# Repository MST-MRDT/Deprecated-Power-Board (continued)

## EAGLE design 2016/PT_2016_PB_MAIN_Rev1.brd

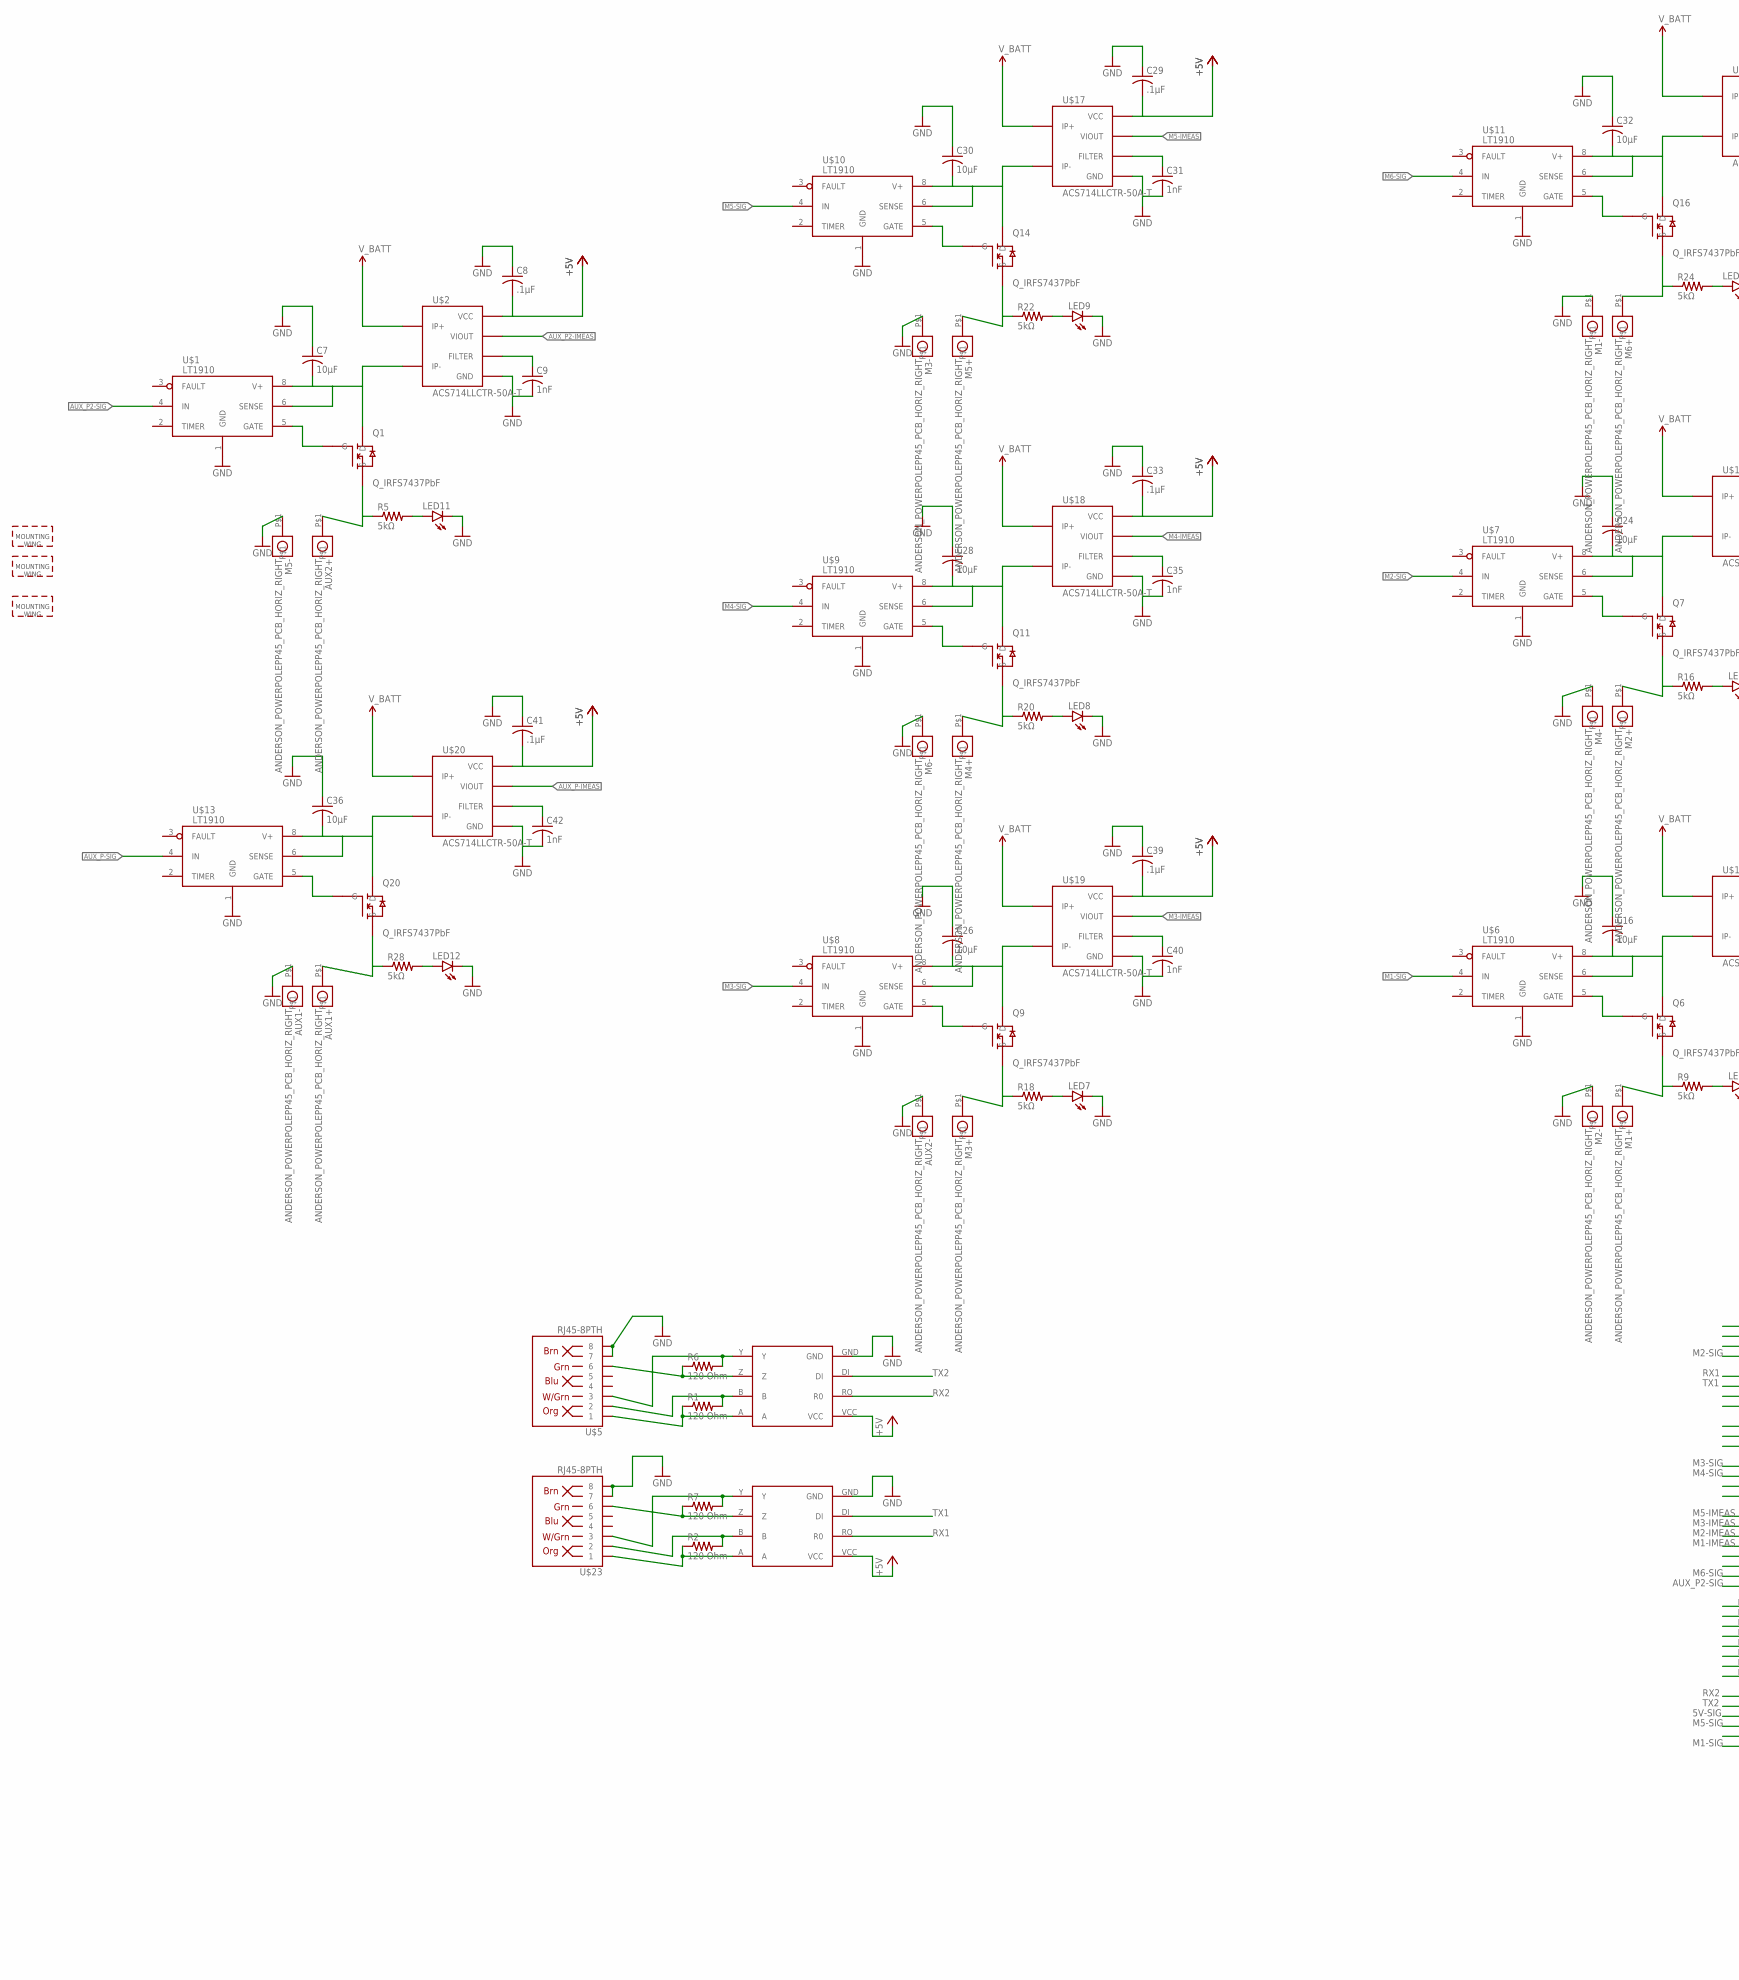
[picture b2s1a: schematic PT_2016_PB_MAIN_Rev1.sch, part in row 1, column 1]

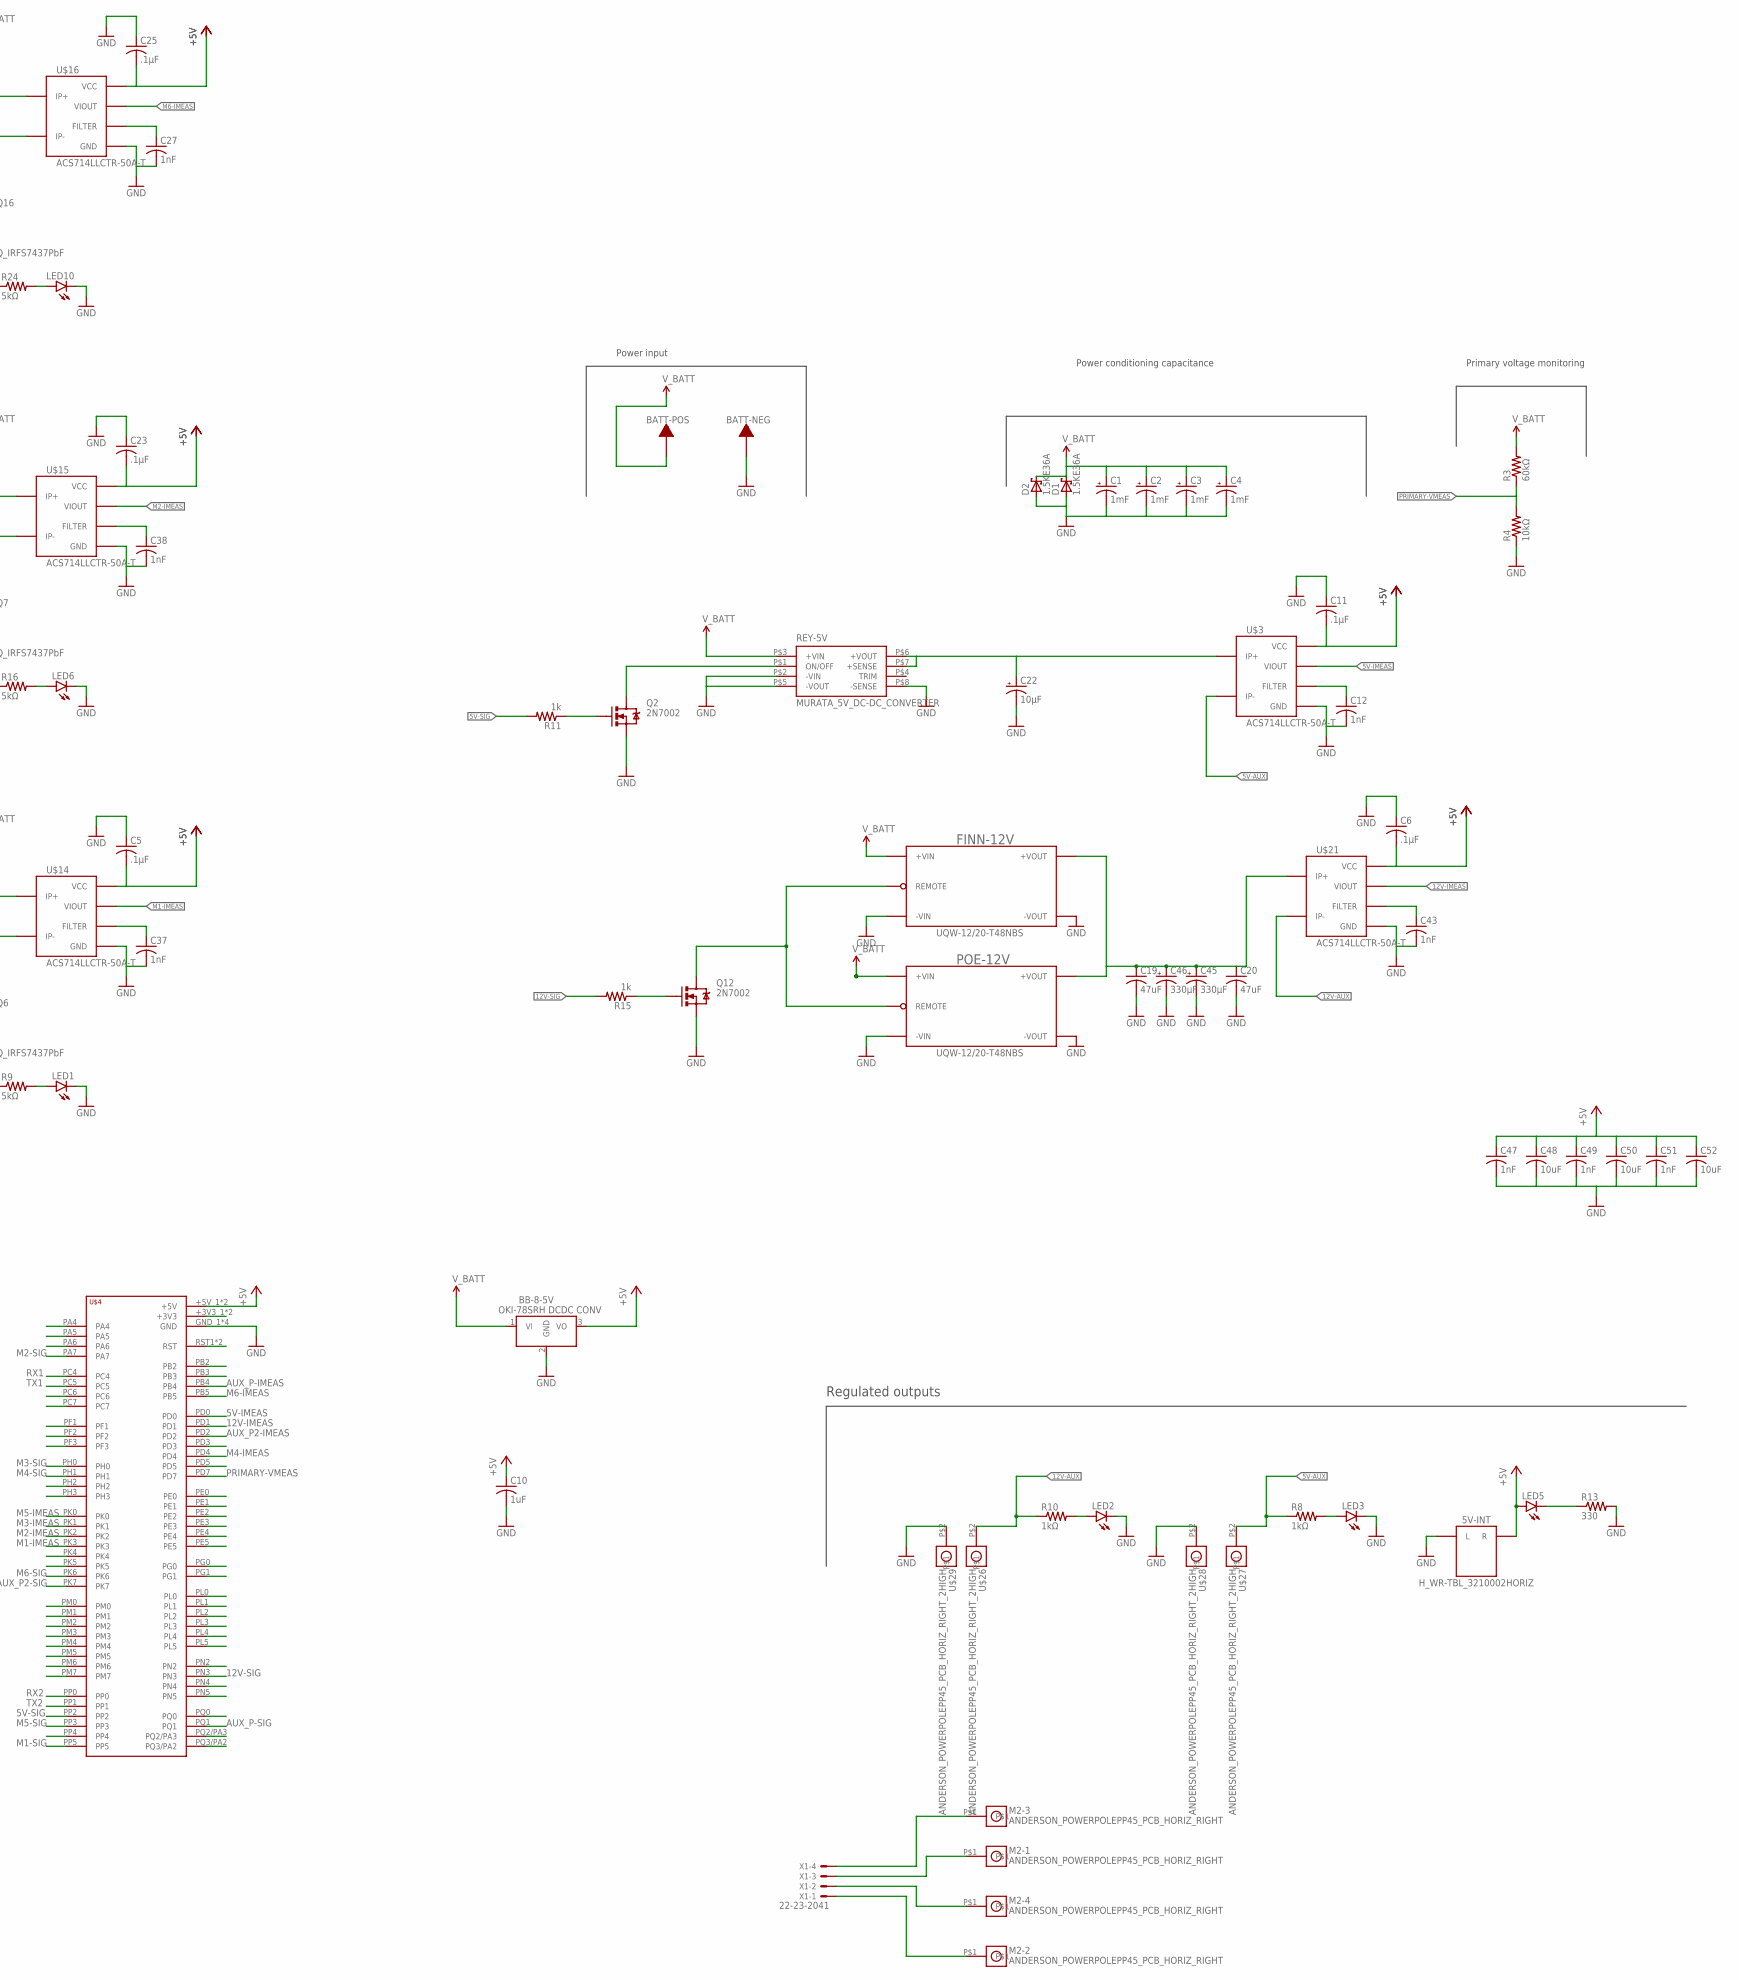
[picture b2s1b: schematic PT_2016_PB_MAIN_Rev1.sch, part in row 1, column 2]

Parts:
5V-INT: H_WR-TBL_3210002HORIZ; 691322110002
AUX1+, AUX1-, AUX2+, AUX2-: ANDERSON_POWERPOLEPP45_PCB_HORIZ_RIGHT; APP45_PCB_HORIZ_RIGHT
BATT-NEG: TERMINAL_HOLE; LARGE_TERMINAL_HOLE
BATT-POS: TERMINAL_HOLE; LARGE_TERMINAL_HOLE
BB-8-5V: Q_OKI-78SR; OKI-78SRH
C1, C2, C3, C4: 1mF; C_12.5MM
C5, C6, C8, C11, C23, C25, C29, C33, C39, C41: .1µF; C1206
C7, C16, C24, C26, C28, C30, C32, C36: 10µF; C1206
C9, C12, C27, C31, C35, C37, C38, C40, C42, C43, C47, C49, C51: 1nF; C1206
C10: 1uF; C1206
C19, C20: 47uF; C1206
C22: 10µF; E5-8,5
C45, C46: 330µF; E5-8,5
C48, C50, C52: 10uF; C1206
D1, D2: 1.5KE36A; CB429-17
FINN-12V: UQW-12/20-T48NBS; U-T48-QB-NO_TRIM
LED1, LED2, LED3, LED5, LED6, LED7, LED8, LED9, LED10, LED11, LED12: LED1206; LED-1206
M1+, M1-, M2+, M2-, M2-1, M2-2, M2-3, M2-4, M3+, M3-, M4+, M4-, M5+, M5-, M6+, M6-: ANDERSON_POWERPOLEPP45_PCB_HORIZ_RIGHT; APP45_PCB_HORIZ_RIGHT
POE-12V: UQW-12/20-T48NBS; U-T48-QB-NO_TRIM
Q1, Q6, Q7, Q9, Q11, Q14, Q16, Q20: Q_IRFS7437PbF; D2PACK
Q2, Q12: 2N7002; SOT323
R1, R2, R6, R7: 120 Ohm; 1206
R3: 60kΩ; R1206
R4: 10kΩ; R1206
R5, R9, R16, R18, R20, R22, R24, R28: 5kΩ; 1206
R8, R10: 1kΩ; 1206
R11, R15: 1k; R1206
R13: 330; 1206
REY-5V: MURATA_5V_DC-DC_CONVERTER
U$1, U$6, U$7, U$8, U$9, U$10, U$11, U$13: LT1910; SO8
U$2, U$14, U$15, U$16, U$17, U$18, U$19, U$20: ACS714LLCTR-50A-T; SOIC8_ACS711_SKETCH
U$3, U$21: ACS714LLCTR-50A-T; SOIC8_ACS711
U$4: TIVA-C-CONNECTED
U$5, U$23: RJ45-8PTH; RJ45-8
U$12, U$24: MAX3077; MAX3070E
U$25, U$41, U$42: APP_MOUTING_WINGHORIZ; APP45_MOUNTING_WING_HORIZ
U$26, U$27, U$28, U$29: ANDERSON_POWERPOLEPP45_PCB_HORIZ_RIGHT_2HIGH; APP45_PCB_HORIZ_RIGHT_2HIGH
X1: 22-23-2041

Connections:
5V-AUX: R8.1, U$3.4 (IP-), U$27.P$2
5V-IMEAS: U$3.7 (VIOUT), U$4.PD0
5V-SIG: R11.2, U$4.PP2
12V-AUX: R10.1, U$21.4 (IP-), U$26.P$2
12V-IMEAS: U$4.PD1, U$21.7 (VIOUT)
12V-SIG: R15.2, U$4.PN3
+5V: 5V-INT.R, BB-8-5V.3 (VO), C5.2, C6.2, C8.2, C10.1, C11.2, C23.2, C25.2, C29.2, C33.2, C39.2, C41.2, C47.1, C48.1, C49.1, C50.1, C51.1, C52.1, LED5.A, U$2.8 (VCC), U$3.8 (VCC), U$4.+5V_1 (+5V), U$4.+5V_2 (+5V), U$12.VCC, U$14.8 (VCC), U$15.8 (VCC), U$16.8 (VCC), U$17.8 (VCC), U$18.8 (VCC), U$19.8 (VCC), U$20.8 (VCC), U$21.8 (VCC), U$24.VCC
AUX_P2-IMEAS: U$2.7 (VIOUT), U$4.PD2
AUX_P2-SIG: U$1.4 (IN), U$4.PK7
AUX_P-IMEAS: U$4.PB4, U$20.7 (VIOUT)
AUX_P-SIG: U$4.PQ1, U$13.4 (IN)
GND: 5V-INT.L, AUX1-.P$1, AUX2-.P$1, BATT-NEG.P$1, BB-8-5V.2 (GND), C1.-, C2.-, C3.-, C4.-, C5.1, C6.1, C7.1, C8.1, C9.2, C10.2, C11.1, C12.2, C16.1, C19.2, C20.2, C22.-, C23.1, C24.1, C25.1, C26.1, C27.2, C28.1, C29.1, C30.1, C31.2, C32.1, C33.1, C35.2, C36.1, C37.2, C38.2, C39.1, C40.2, C41.1, C42.2, C43.2, C45.-, C46.-, C47.2, C48.2, C49.2, C50.2, C51.2, C52.2, D1.A, D2.A, FINN-12V.3 (-VIN), FINN-12V.4 (-VOUT), LED1.C, LED2.C, LED3.C, LED6.C, LED7.C, LED8.C, LED9.C, LED10.C, LED11.C, LED12.C, M1-.P$1, M2-.P$1, M3-.P$1, M4-.P$1, M5-.P$1, M6-.P$1, POE-12V.3 (-VIN), POE-12V.4 (-VOUT), Q2.2 (S), Q12.2 (S), R4.1, R13.2, REY-5V.P$2 (-VIN), REY-5V.P$5 (-VOUT), REY-5V.P$8 (-SENSE), U$1.1 (GND), U$2.5 (GND), U$3.5 (GND), U$4.GND_1 (GND), U$4.GND_2 (GND), U$4.GND_3 (GND), U$4.GND_4 (GND), U$5.7, U$5.8, U$6.1 (GND), U$7.1 (GND), U$8.1 (GND), U$9.1 (GND), U$10.1 (GND), U$11.1 (GND), U$12.GND, U$13.1 (GND), U$14.5 (GND), U$15.5 (GND), U$16.5 (GND), U$17.5 (GND), U$18.5 (GND), U$19.5 (GND), U$20.5 (GND), U$21.5 (GND), U$23.7, U$23.8, U$24.GND, U$28.P$2, U$29.P$2
M1-IMEAS: U$4.PK3, U$14.7 (VIOUT)
M1-SIG: U$4.PP5, U$6.4 (IN)
M2-IMEAS: U$4.PK2, U$15.7 (VIOUT)
M2-SIG: U$4.PA7, U$7.4 (IN)
M3-IMEAS: U$4.PK1, U$19.7 (VIOUT)
M3-SIG: U$4.PH0, U$8.4 (IN)
M4-IMEAS: U$4.PD4, U$18.7 (VIOUT)
M4-SIG: U$4.PH1, U$9.4 (IN)
M5-IMEAS: U$4.PK0, U$17.7 (VIOUT)
M5-SIG: U$4.PP3, U$10.4 (IN)
M6-IMEAS: U$4.PB5, U$16.7 (VIOUT)
M6-SIG: U$4.PK6, U$11.4 (IN)
unnamed: C37.1, U$14.6 (FILTER)
unnamed: C38.1, U$15.6 (FILTER)
unnamed: M2-3.P$1, X1.4
unnamed: FINN-12V.2 (REMOTE), POE-12V.2 (REMOTE), Q12.3 (D)
unnamed: M2-1.P$1, X1.3
unnamed: LED5.C, R13.1
unnamed: C22.+, REY-5V.P$6 (+VOUT), REY-5V.P$7 (+SENSE), U$3.1 (IP+)
unnamed: M2-4.P$1, X1.2
unnamed: C7.2, Q1.TAB (D), U$1.6 (SENSE), U$1.8 (V+), U$2.4 (IP-)
unnamed: AUX2+.P$1, Q1.2 (S), R5.1
unnamed: M2-2.P$1, X1.1
unnamed: C43.1, U$21.6 (FILTER)
unnamed: Q1.1 (G), U$1.5 (GATE)
unnamed: LED11.A, R5.2
unnamed: C9.1, U$2.6 (FILTER)
unnamed: C27.1, U$16.6 (FILTER)
unnamed: C31.1, U$17.6 (FILTER)
unnamed: C35.1, U$18.6 (FILTER)
unnamed: C40.1, U$19.6 (FILTER)
unnamed: C42.1, U$20.6 (FILTER)
unnamed: C24.2, Q7.TAB (D), U$7.6 (SENSE), U$7.8 (V+), U$15.4 (IP-)
unnamed: M2+.P$1, Q7.2 (S), R16.1
unnamed: Q7.1 (G), U$7.5 (GATE)
unnamed: LED6.A, R16.2
unnamed: C19.1, C20.1, C45.+, C46.+, FINN-12V.8 (+VOUT), POE-12V.8 (+VOUT), U$21.1 (IP+)
unnamed: LED3.A, R8.2
unnamed: C12.1, U$3.6 (FILTER)
unnamed: LED1.A, R9.2
unnamed: C16.2, Q6.TAB (D), U$6.6 (SENSE), U$6.8 (V+), U$14.4 (IP-)
unnamed: M1+.P$1, Q6.2 (S), R9.1
unnamed: Q6.1 (G), U$6.5 (GATE)
unnamed: Q2.3 (D), REY-5V.P$1 (ON/OFF)
unnamed: C26.2, Q9.TAB (D), U$8.6 (SENSE), U$8.8 (V+), U$19.4 (IP-)
unnamed: M3+.P$1, Q9.2 (S), R18.1
unnamed: LED2.A, R10.2
unnamed: Q9.1 (G), U$8.5 (GATE)
unnamed: Q2.1 (G), R11.1
unnamed: LED7.A, R18.2
unnamed: C28.2, Q11.TAB (D), U$9.6 (SENSE), U$9.8 (V+), U$18.4 (IP-)
unnamed: M4+.P$1, Q11.2 (S), R20.1
unnamed: Q11.1 (G), U$9.5 (GATE)
unnamed: LED8.A, R20.2
unnamed: C30.2, Q14.TAB (D), U$10.6 (SENSE), U$10.8 (V+), U$17.4 (IP-)
unnamed: M5+.P$1, Q14.2 (S), R22.1
unnamed: Q14.1 (G), U$10.5 (GATE)
unnamed: LED9.A, R22.2
unnamed: C32.2, Q16.TAB (D), U$11.6 (SENSE), U$11.8 (V+), U$16.4 (IP-)
unnamed: M6+.P$1, Q16.2 (S), R24.1
unnamed: Q16.1 (G), U$11.5 (GATE)
unnamed: LED10.A, R24.2
unnamed: C36.2, Q20.TAB (D), U$13.6 (SENSE), U$13.8 (V+), U$20.4 (IP-)
unnamed: AUX1+.P$1, Q20.2 (S), R28.1
unnamed: Q20.1 (G), U$13.5 (GATE)
unnamed: LED12.A, R28.2
unnamed: U$4.+3V3_1 (+3V3), U$4.+3V3_2 (+3V3)
unnamed: U$4.RST1 (RST), U$4.RST_2 (RST)
unnamed: Q12.1 (G), R15.1
PRIMARY-VMEAS: R3.1, R4.2, U$4.PD7
REC+: R1.1, U$5.1, U$12.A
REC+1: R2.1, U$23.1, U$24.A
REC-: R1.2, U$5.2, U$12.B
REC-1: R2.2, U$23.2, U$24.B
RX1: U$4.PC4, U$24.RO (R0)
RX2: U$4.PP0, U$12.RO (R0)
TRANS+: R6.2, U$5.3, U$12.Y
TRANS+1: R7.2, U$23.3, U$24.Y
TRANS-: R6.1, U$5.6, U$12.Z
TRANS-1: R7.1, U$23.6, U$24.Z
TX1: U$4.PC5, U$24.DI
TX2: U$4.PP1, U$12.DI
V_BATT: BATT-POS.P$1, BB-8-5V.1 (VI), C1.+, C2.+, C3.+, C4.+, D1.C, D2.C, FINN-12V.1 (+VIN), POE-12V.1 (+VIN), R3.2, REY-5V.P$3 (+VIN), U$2.1 (IP+), U$14.1 (IP+), U$15.1 (IP+), U$16.1 (IP+), U$17.1 (IP+), U$18.1 (IP+), U$19.1 (IP+), U$20.1 (IP+)

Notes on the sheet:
Primary voltage monitoring
Power conditioning capacitance
Power input
Regulated outputs

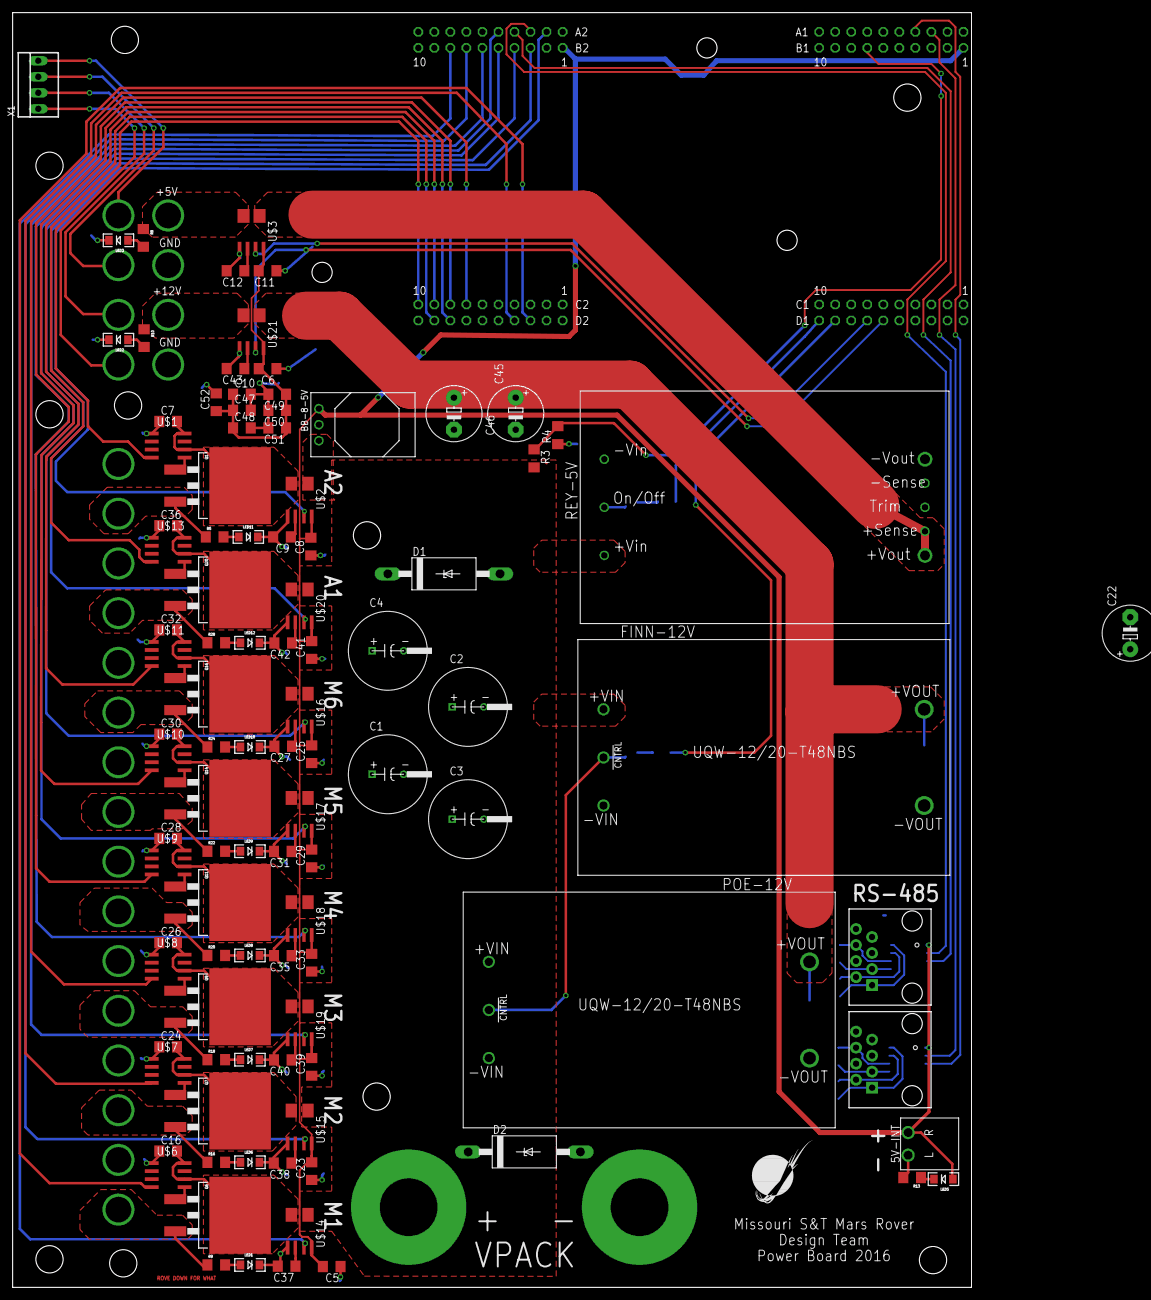
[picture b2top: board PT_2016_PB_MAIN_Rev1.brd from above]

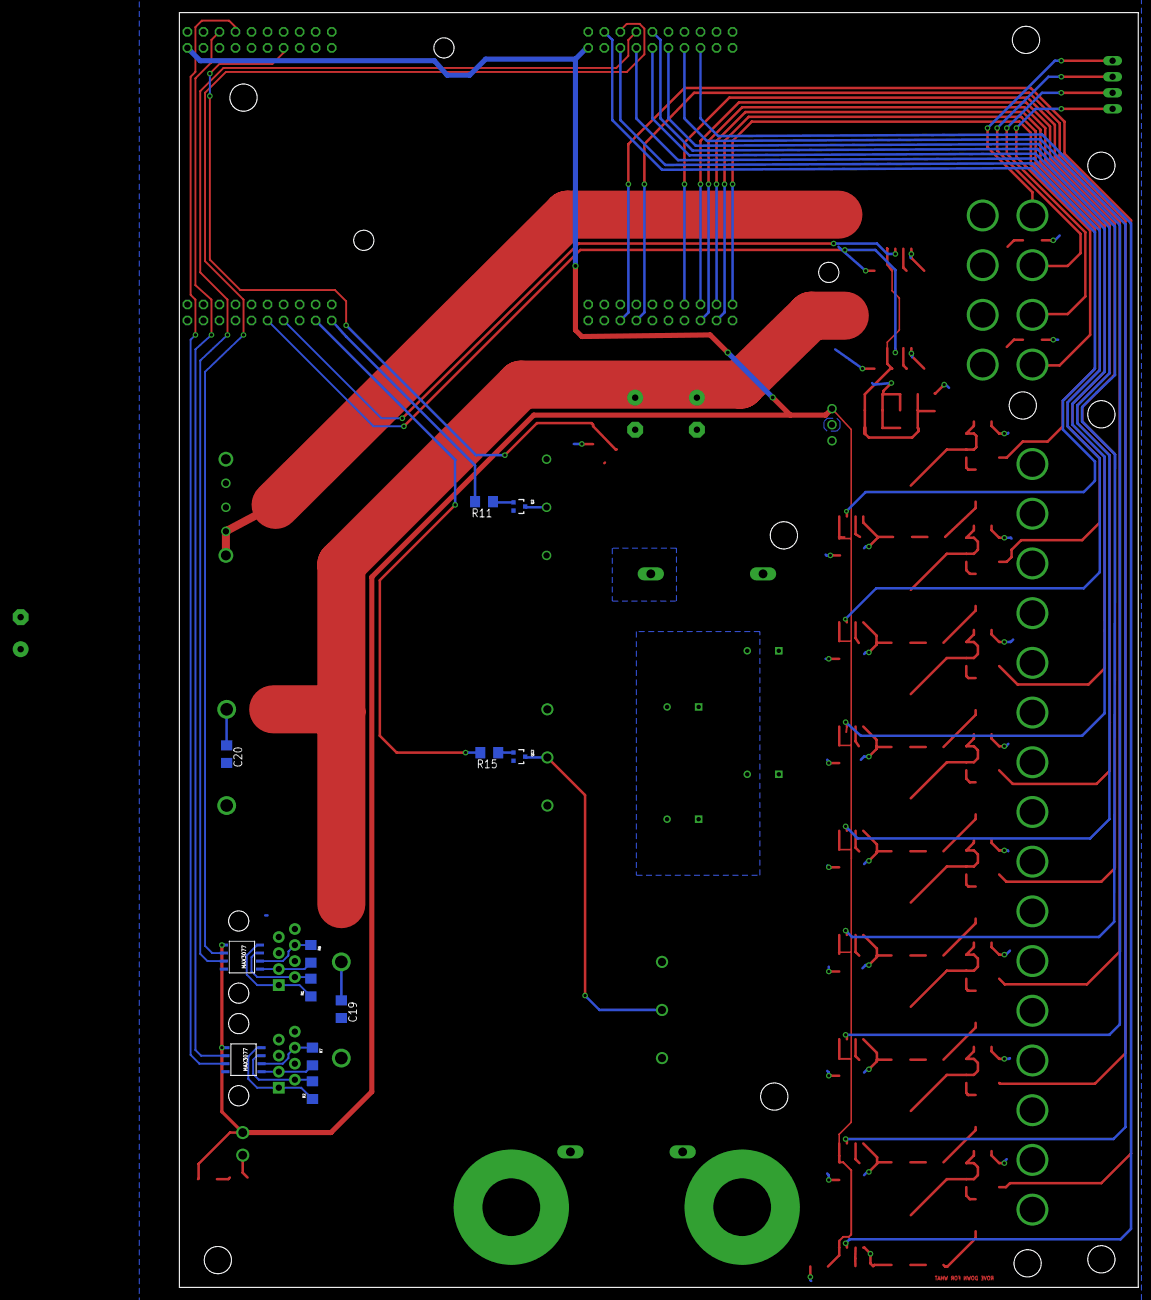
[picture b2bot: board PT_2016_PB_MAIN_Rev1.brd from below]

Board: 2 copper layers, 151.9 x 201.9 mm, 145 parts (15 on the bottom side), 95 nets.

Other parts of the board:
U$22: MRDT_LOGO

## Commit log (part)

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2016-01-17 New Layout Idea
2016-01-17 Routed new layout
2016-01-18 Jake started routing 4 layer board
2016-01-18 Changed 5V Caps
2016-01-18 rerouting...
2016-01-19 Finished routing 4-layer
2016-01-21 github sucks
2016-01-21 FINAL REV2 - ORDERED SIERRA CIRCUITS
    didnt actually change anything
2016-02-11 osh stencil gerbers
2016-03-13 Moved around 12v bucks, routed ORing mosfet circuits
2016-03-13 Changed ORing FETs to DPAK
2016-04-05 Routed, moved some motor fets over
2016-04-10 Changed 5V on/off circuit, enlarged planes
2016-04-11 Final Power Board 2016 Rev 2
    generated gerbers
2016-04-16 Swapped LM74670 with LM5050
2016-04-17 Generated gerbers
2016-04-20 Improved some top planes
2017-10-04 Added 2014 branch so I can release the 2014 files
2017-10-04 added 2015 specific branch so I can draft a release
2019-10-02 Pass 1.2
    *Circuit has been consolidated
    *All 6 circuits have been added
2019-10-04 Pass 1.4
    *Fuses have been added after each anderson
2019-10-09 Pass 1.5
    *pvv changed to PVDD
    *Fuses placed before each anderson
    *pcb layout generated
    *PVDD via has issues
2019-11-12 Pass 1.7
2019-12-13 Overwriting for proper file structure
2019-12-14 Ready for PRR
2019-12-14 made schematic prettier
2019-12-14 fixed schematic b/c Zac made fun of me
2019-12-19 Regenerated gerbs (No drill files Iguess)
2020-01-21 Created step file
2020-02-07 All 3V3 connected, need to fix silkscreen and move connectors
2020-02-15 Ready for Rev 2 review, minus frame ground
2020-02-17 updated gerbs
2020-09-14 Added Folders
2020-09-30 Tiva Schematic
2020-10-02 Started Current and LT1910 circuits
    Mosfet and current sensor for one port made
2020-10-05 Busses
    Continued wiring driver, busses, and current sensors on sheet 2
2020-10-05 Rearranging
    slight changes to wire placement, no major changes
2020-10-13 added hierarchical labels, changed current sensor, added 12V labels to TIVA, finished buck sheet
2020-10-14 Extra Bus, Connectors moved to top level
    Added "Extra" 20A bus, tiva pins, and anderson
    Moved molex connector out of tiva sheet so it is visible on top sheet
    Removed "Power In" sheet to bring vias to top sheet.
2020-10-15 Added 5th Motor
    Added Motor 5 to Motor Busses, added tiva pins and anderson connections
    Renamed Extra 5 to Extra 6
2020-10-15 Matching 12V Tiva Pins
    Renamed 12 tiva pins to match their names on 12V board
    Changed molex connections to match those on 12V board
    Removed LowExtra_CTL as it is not present on 12V connector
2020-10-15 updated busses, fuses, and some names
2020-10-16 Fixed Hierarchial Pins/Labels
    Removed Hierarchal labels from top sheet and replaced them with pins linked to the subsheets.
    Renamed M5 Tiva pin to D1
2020-10-22 Updated molex connector (Still need tiva pin)
2020-10-23 Rearranged Bucks and Fixed 12V Bus LED Resistor
    Moved 5v bus to the middle and 3.3V bus to the bottom to make things more clear.
    12 bus had 3300 ohm resistor when it should have 1200 ohm b/c it only has 12 V going into it
2020-10-26 Added GimbalSense, reannotated
2020-10-29 Added Footprints (Still missing MOSFET)
2020-11-07 Changed capacitor footprints
    Changed 1000uF and 470uF capacitor footprints. Imported footprint for 470uF so it might need looking at.
    Changed unpolarized 1000uF capacitors in bucks to polarized capacitors
2020-11-15 started editing layout
2020-11-16 Layout
2020-11-17 Rearranging Planes
2020-11-17 added auxillary components to layout
2020-11-17 Added Driveboard Bus, Fixed Pads
2020-11-18 rearranged components on layout
2020-11-18 Added Planes to Aux, Vaccum, 12V busses, started swapping shunt resistors and sensors
2020-11-19 added all components to board
2020-11-19 Finished Busses, Fixed Vias in Pads, Connected Okis & Buck
2020-11-22 Rocket and 12V bus connected
2020-11-22 All Busses connected to Tiva, LEDs connected
2020-11-23 labelled LEDs
2020-11-23 3D graphics
2020-11-26 Made room for mounting holes
2020-11-27 Moved vias, changed isolated pad of resistors to no net
2020-11-27 Added signature folder and my signature to board
2020-11-27 Tiva pins
2020-11-27 Moved PV plane from under mounting hole
2020-11-29 started BOM file
2020-12-04 footprint update
    -andersons made vertical
    -current resistor footprint updated
2020-12-07 Buck Layout
2020-12-07 12 Tiva pins rearranged
2020-12-08 Tiva Layout updated
2020-12-10 motors
    changed name of components in layout to match schematic
2020-12-11 Tiva pins connected, okis connected
2020-12-11 Updated Silkscreen
2020-12-14 updated BOM
2020-12-14 Completed Gerbs
2021-01-05 BOM updated
    some components were chosen incorrectly
2021-02-18 changed mosfet footprint so its actually right
2021-03-12 updated mosfet footprints
    but for real this time
2021-03-12 rearranged components (layout)
2021-03-19 circuit, deletes
    made circuit to copy across board (hopefully);
    deleted old traces that "aren't wide enough"
2021-03-20 uhh more circuits
    finished top circuits on layout, fixed two resistors in schematic
2021-03-22 finished circuits
    finished main circuits
2021-03-22 molexes
    - changed 5 pin molex to 4 pin molex (removed buckCTL)
    - started making traces from molexes to tiva
2021-03-23 mounting holes
    got placed
2021-04-10 gerbs made
2021-04-28 Revert "netlist"
    This reverts commit 1af6446f6858f10edba603e339066d14f3a2f95b.
2021-04-28 netlist for power andersons
2021-10-01 Finished bucks & started implementation of the TIVA
2021-10-06 Added sheets for 12V
2021-10-07 Added other pack MOSFETS
2021-10-08 Created global tags in main sheet
2021-10-10 Fixed some stuff
2021-10-21 Minor changes with Powerboard PDF
2021-10-21 Minor changes
2021-11-11 Assigned Footprints to Symbols
2021-11-12 Made it to layout, found out about gnd via
2021-11-12 Started on the layout of the board
    Made the outline of the board, organized anderson connections so they are easily distinguishable, and added ground planes on front and back copper
2021-11-12 Organized parts
2021-11-12 fixed Fuses
2021-11-13 Revert Previous merge
2021-11-13 Layout changes
2021-11-14 Revert "Placed Components for Motor 1 and fixed errors with netlist"
    This reverts commit 86a32237b1b6d07fe668dfe10dac6f9ef44dc23b.
2021-11-14 Fixed a few errors and started wiring motor 1
2021-11-14 Wired connections for a couple of motors
2021-11-15 wires for motor 1
2021-11-16 Added SciAct to the Board
2021-11-16 Rearranged layout to keep actuation next to logic
2021-11-16 Started placing GimAct components
2021-11-17 Changed a lot, made the whole ass front plane pack, and questioned everything
2021-11-17 Organized
2021-11-17 Connected GND pads to GND
2021-11-17 Fixed and wired first four motor circuits
2021-11-17 Connected the TIVA to PVACT1, PVACT2, Pack, and PV2
2021-11-17 Added tag for circuits
2021-11-18 Worked on Cam 1 & 2 and started with Multimedia
2021-11-18 Added more sikscreen stuff
2021-11-21 double all of the anderson names, and fuse ratings.
2021-11-21 PV is not needed in the center of the board, change the PV plane to be a U shape and have the center of that (on the front plane) be gnd instead
2021-11-28 Changed Anderson Plane Sizes to .25'' or higher
2021-11-29 Net plane changes
2021-11-30 Replaced 12v okis w/big buck. Changed .0025 resistors to not 603.
2021-11-30 Fixed tags
2021-12-03 changed MOSFET names to what we're actually using
2021-12-04 Closing kicad + bom stuff
2021-12-05 Changed the footprint for the shunt resistors and loaded the netlist to the layout
2021-12-05 Cleaned up board and set dimensions with new board size
2021-12-05 Finished example for PV circuit and moved TIVA layout
2021-12-05 added screw holes
2021-12-11 Organized PV M1 Circuit
2021-12-11 Added GND and PV planes and organized everything onto the board except for 12V circuits
2021-12-12 Did a lot of shit Pt.1
2021-12-12 Did a lot of shit Pt.2
2021-12-13 Connected the TIVA up
2021-12-17 fixed gimbal anderson (tentative on the field changes)
2021-12-17 Cleared wire connections and set up board for new connections
2021-12-22 Brought all the connections from the components closer to the location of the TIVA
2021-12-22 added ground planes for the two middle layers
2022-02-11 Fixed the labels on the drive anderson and fixed U61 & C106 not being grounded
2022-02-11 Grounded OKI LEDS
2022-02-17 added motors, okis, vias, and teensy
2022-02-18 fixed anderson tags
2022-02-18 added 12V anderson
2022-02-26 Cleaned up main page and added POE Current sense and driver
2022-02-26 Changed Resistor Values Pt.2
2022-03-08 Implementing the tiva into Pack
2022-03-08 Tiva changes, just driver pins now.
2022-03-09 saving
2022-03-10 Back to TEENSY
2022-03-10 Organizing stuff
2022-03-10 assigned Molex footprints
2022-03-12 Somewhat completed schematic
    did stuff
2022-03-13 Wired a few circuits, mainly oki and ethernet and M1
2022-03-13 Added all the components to the board and began wiring them together
2022-03-15 more wiring
2022-03-18 fixed schematic issues - renamed ports, removed unnecessary ports, corrected footprint assignments; began layout - created circuits for most ports, most components placed
2022-03-18 All connections made
2022-04-06 Generated step file
2022-09-24 finished schematic
2022-09-24 Added Fuses
2022-09-26 Made Most of the Review Changes
2022-10-02 Assigned Footprints
2022-10-11 Added Fuses, Potential Layout for Connector 1
2022-10-11 Placed Power Vias, Set Up Oki and Power Filter
2022-10-16 MOSFET Layouts
2022-10-23 Traces and silkscreen
2022-10-28 Layout edits
2022-11-06 Layout Review Changes
2022-11-07 updates ;)
2022-11-11 edits
    added 3d fuse blocks ;P
2022-11-19 generated Gerbs
2023-01-13 added pull down resistors to gates of nfets
2023-01-29 Fixed Resistor Values
2023-02-08 Made Schematic Review Changes
2023-03-03 20A Current Sensing Blocks on Layout
2023-03-15 Further progress on port blocks in layout
2023-03-15 More layout, mostly done except signal traces
2023-03-19 Layout done except ethernet and vias
2023-03-20 High current ports reblocked with 4-layer board
2023-03-20 more layout
2023-03-20 Layout Finished
2023-03-21 generated gerbs and fixed files
2023-04-21 New Schematic, Added 12V and Battery Backup
2023-04-22 Components Arranged on Layout
2023-04-22 Layout Traces Finished
2023-09-08 2024 Rev1
    Created 2024 Rev1 Branch
    Outlined main features on schematic
2023-09-13 troubleshooting push issues
    added an anderson
2023-09-13 test push again
    added another anderson
2023-09-18 Changes
    New Current Sensing Component
    Mosfet Resistor values change
    Still needs plenty of work
2023-09-25 Schematic Changes P1
    Current Sensing Changes
    24V Converter
2023-09-25 Schematic Changes P3
    Current Sensing Stuff
    Other Stuff
2023-09-29 10K 5A V.Div. Revision
    removed 3 3.3K and 3 6.8K and replace with 6 10K resistors
2023-10-03 Finished Adding NetSwitch3 24V Buck
    -Both 24V buck capacitors changed to correct value.
    -Made Net Switch_3 24V buck have its own global variable for 24V output.
    -Moved global label slightly off of teensy pins so a bit of wire is showing.
    -I believe I removed the unnecessary 24V buck trace.
    IMPORTANT NOTICE
    NetSwitch3 Current Sensing variable hasn't been connected to the teensy because the teensy is out of analog spots. Garret said he'll look at it and let us know where to put it.
2023-10-08 Layout Started
    Fixed footprints
    Started Layout
    Lots of work left to be done
2023-10-11 Fill gnd plane
    discussed stuff & goofed
2023-10-15 Layout Stuff Rev1
2023-10-15 Layout Review Ready
    Made the traces pretty
2023-10-20 I changed the C6 to 1206 from 0603
    cap rated 35v, sees PV = needed to change cap = must alter footprint
2023-10-31 Organize components
2023-10-31 Layout Traces
    Finished Trace Work
    Added Signature
2023-11-01 Added Dylan Dush Signature
    I added my signature of 20mm x 7.4mm.
2023-11-01 Silkscreens
2023-11-01 Added my signature
    :)
2023-11-02 Added PV and GND Silkscreen
2023-11-03 Finished Third Review Layout
2023-11-08 User Drawings
2023-11-10 PFET Change
    Changed PFET
    Generated Gerbs
